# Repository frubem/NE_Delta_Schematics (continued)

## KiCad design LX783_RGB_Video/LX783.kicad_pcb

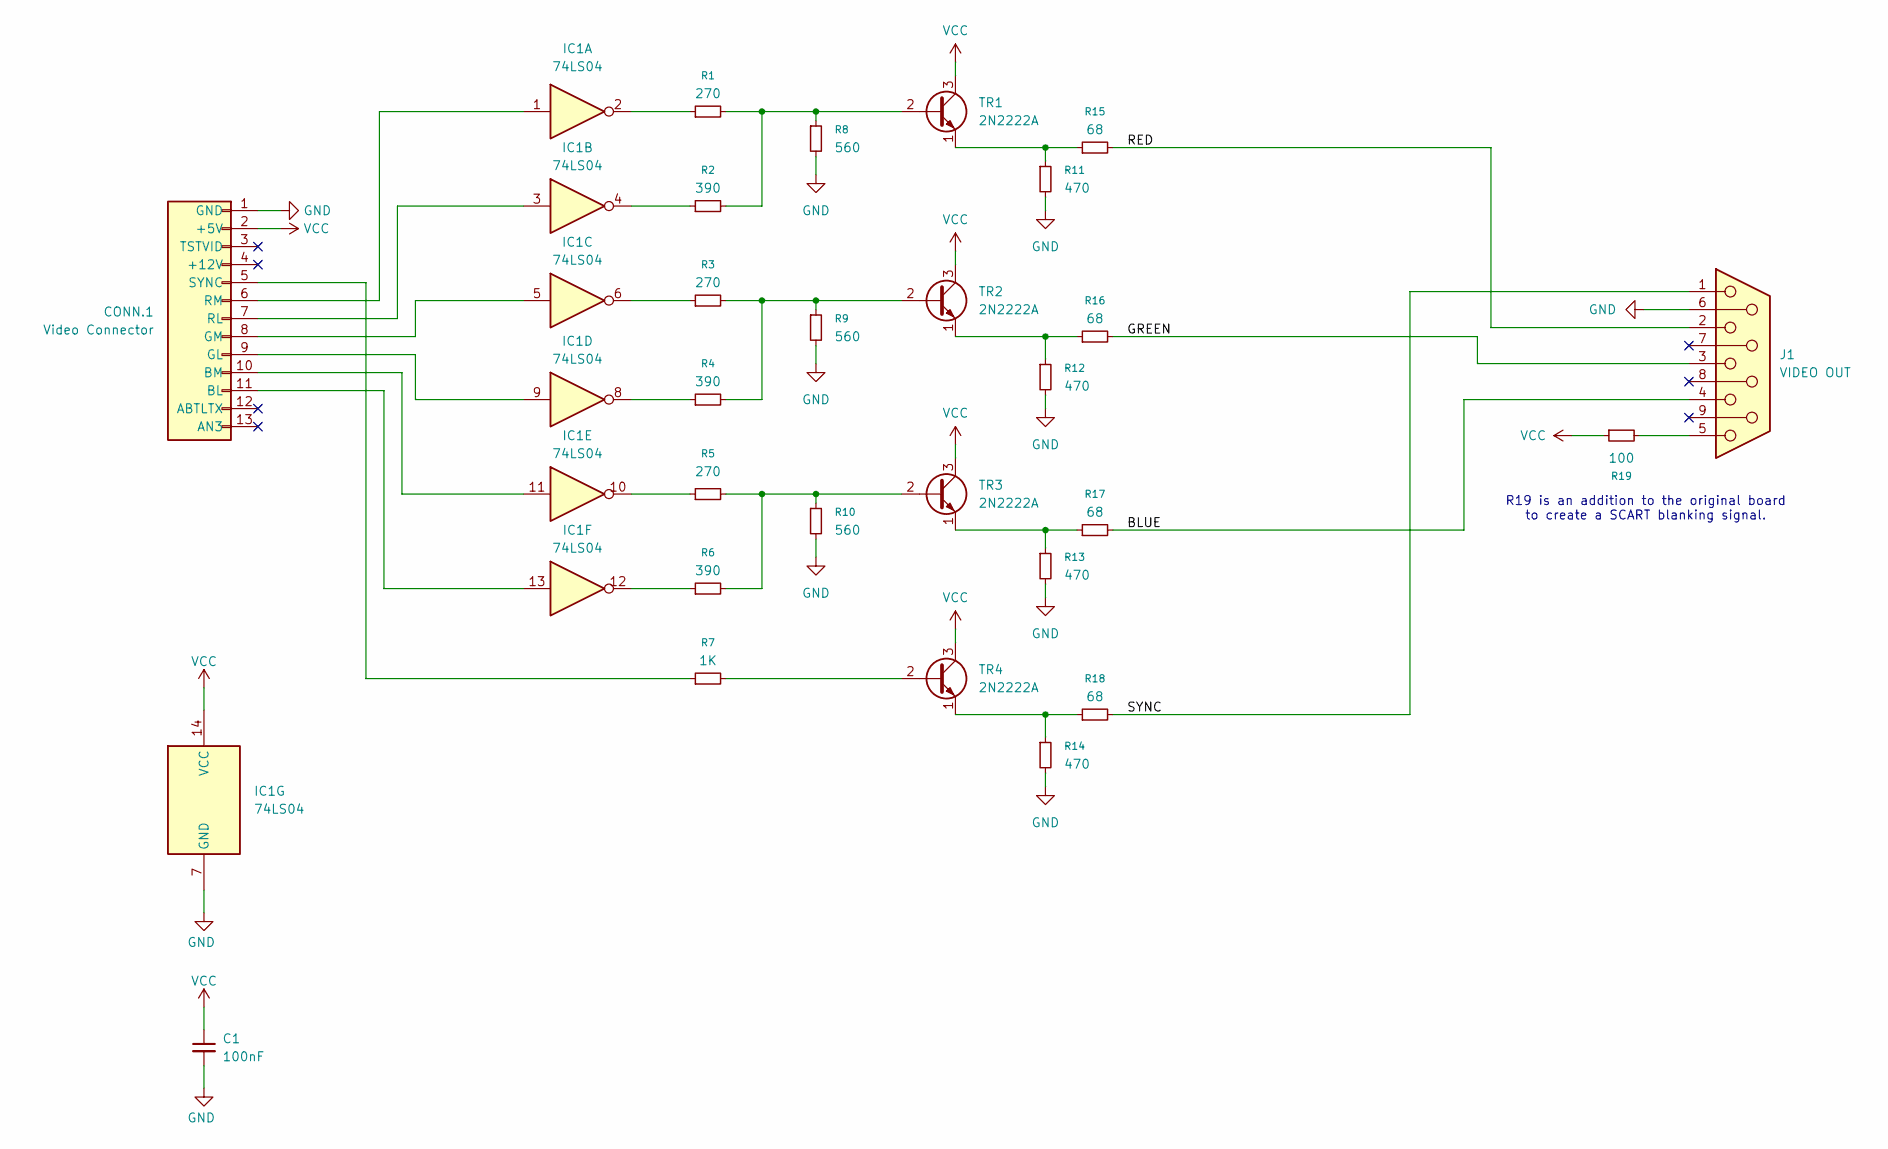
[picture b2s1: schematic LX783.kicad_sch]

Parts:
C1: 100nF; C_Disc_D6.0mm_W2.5mm_P5.00mm
CONN.1: Video Connector; PinHeader_1x13_P2.54mm_Horizontal
IC1: 74LS04; DIP-14_W7.62mm
J1: VIDEO OUT; DSUB-9_Socket_Horizontal
R1, R3, R5: 270; R_Axial_DIN0309_L9.0mm_D2.87mm_P12mm_Horizontal
R2, R4, R6: 390; R_Axial_DIN0309_L9.0mm_D2.87mm_P12mm_Horizontal
R7: 1K; R_Axial_DIN0309_L9.0mm_D2.87mm_P12mm_Horizontal
R8, R9, R10: 560; R_Axial_DIN0309_L9.0mm_D2.87mm_P12mm_Horizontal
R11, R12, R13, R14: 470; R_Axial_DIN0309_L9.0mm_D2.87mm_P12mm_Horizontal
R15, R16, R17, R18: 68; R_Axial_DIN0309_L9.0mm_D2.87mm_P12mm_Horizontal
R19: 100; R_Axial_DIN0309_L9.0mm_D2.87mm_P12mm_Horizontal
TR1, TR2, TR3, TR4: 2N2222A; TO-92_HandSolder

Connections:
/BLUE: J1.4, R17.2
/GREEN: J1.3, R16.2
/RED: J1.2, R15.2
/SYNC: J1.1, R18.2
GND: C1.2, CONN.1.1 (GND), IC1.7 (GND), J1.6, R8.2, R9.2, R10.2, R11.2, R12.2, R13.2, R14.2
unnamed: CONN.1.11 (BL), IC1.13
unnamed: CONN.1.10 (BM), IC1.11
unnamed: CONN.1.9 (GL), IC1.9
unnamed: CONN.1.8 (GM), IC1.5
unnamed: CONN.1.7 (RL), IC1.3
unnamed: CONN.1.6 (RM), IC1.1
unnamed: CONN.1.5 (SYNC), R7.1
unnamed: IC1.2, R1.1
unnamed: IC1.4, R2.1
unnamed: IC1.6, R3.1
unnamed: IC1.8, R4.1
unnamed: IC1.10, R5.1
unnamed: IC1.12, R6.1
unnamed: J1.5, R19.2
unnamed: R1.2, R2.2, R8.1, TR1.2 (B)
unnamed: R11.1, R15.1, TR1.1 (E)
unnamed: R3.2, R4.2, R9.1, TR2.2 (B)
unnamed: R12.1, R16.1, TR2.1 (E)
unnamed: R5.2, R6.2, R10.1, TR3.2 (B)
unnamed: R13.1, R17.1, TR3.1 (E)
unnamed: R7.2, TR4.2 (B)
unnamed: R14.1, R18.1, TR4.1 (E)
VCC: C1.1, CONN.1.2 (+5V), IC1.14 (VCC), R19.1, TR1.3 (C), TR2.3 (C), TR3.3 (C), TR4.3 (C)

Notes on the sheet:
R19 is an addition to the original board to create a SCART blanking signal.

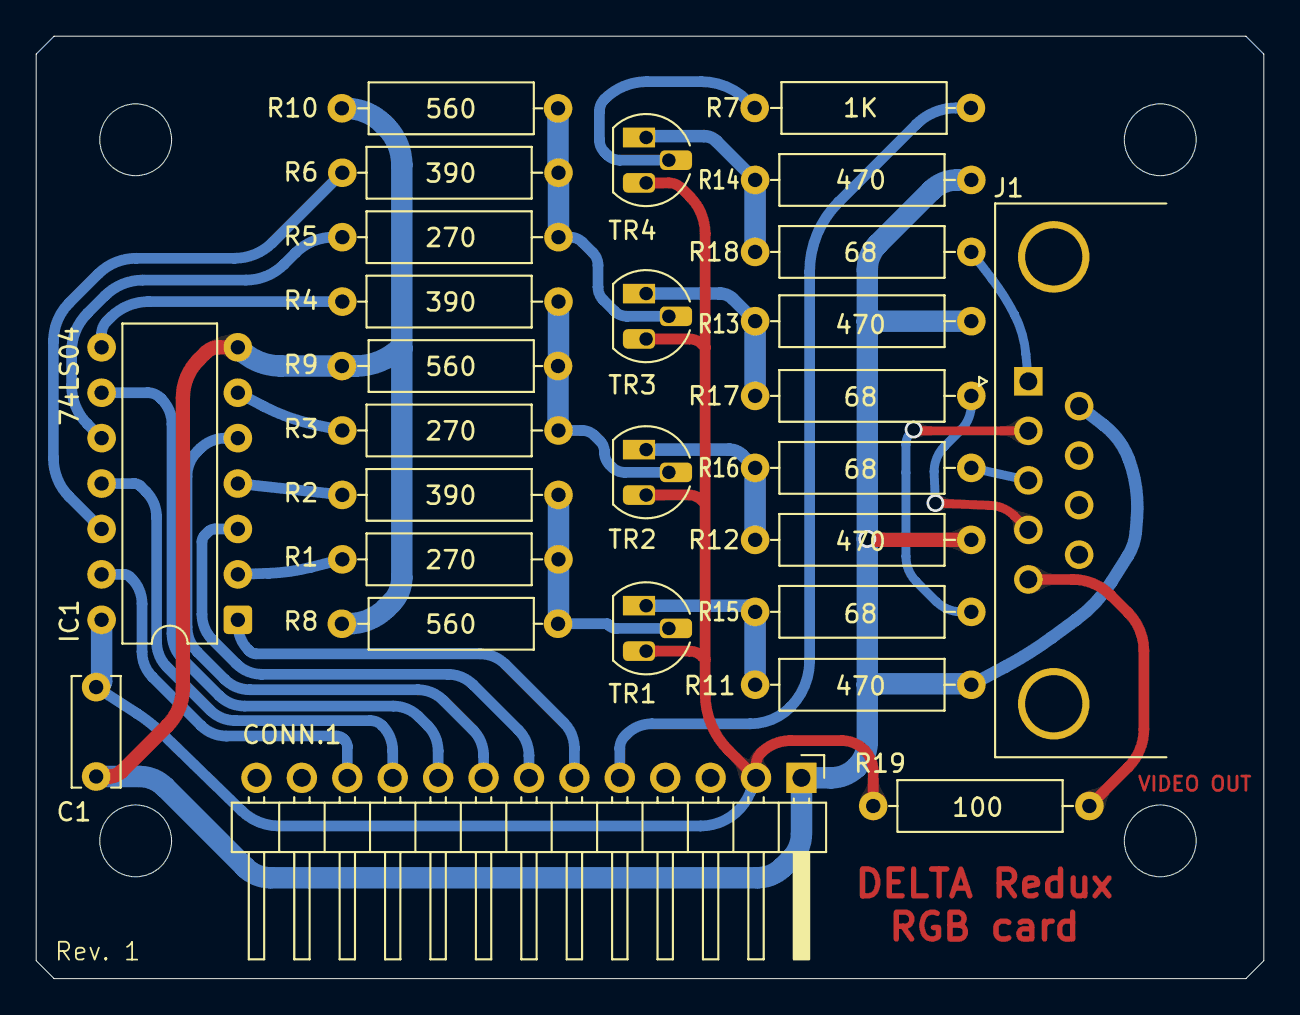
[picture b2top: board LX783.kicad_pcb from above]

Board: 2 copper layers, 68.7 x 52.7 mm, 27 parts (0 on the bottom side), 28 nets.

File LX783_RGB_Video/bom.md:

# LX783 RGB Video board - BOM

| Component              | Qty | Type / Value                                            | Notes                                                                |
| ---------------------- | --- | ------------------------------------------------------- | -------------------------------------------------------------------- |
| C1                     |  1  | 100nF/16V+ MLCC capacitor, 5mm pitch                    |                                                                      |
| CONN.1                 |  1  | pin header, 13P, 2.54mm pitch, right angle              |                                                                      |
| IC1                    |  1  | 74LS04 DIP-14                                           | Make sure to use an LS here, HCT works but colors will be off unless resistor values are adjusted |
| J1                     |  1  | DSUB-9 socket, horizontal                               |                                                                      |
| R1, R3, R5             |  3  | 270ohm resistor, 1/4W                                   |                                                                      |
| R2, R4, R5             |  3  | 390ohm resistor, 1/4W                                   |                                                                      |
| R7                     |  1  | 1Kohm resistor, 1/4W                                    |                                                                      |
| R8, R9, R10            |  3  | 560ohm resistor, 1/4W                                   |                                                                      |
| R11, R12, R13, R14     |  4  | 470ohm resistor, 1/4W                                   |                                                                      |
| R15, R16, R17, R18     |  4  | 68ohm resistor, 1/4W                                    |                                                                      |
| R19                    |  1  | 100ohm resistor, 1/4W                                   |                                                                      |
| TR1, TR2, TR3, TR4     |  4  | 2N2222A, TO-92                                          |                                                                      |

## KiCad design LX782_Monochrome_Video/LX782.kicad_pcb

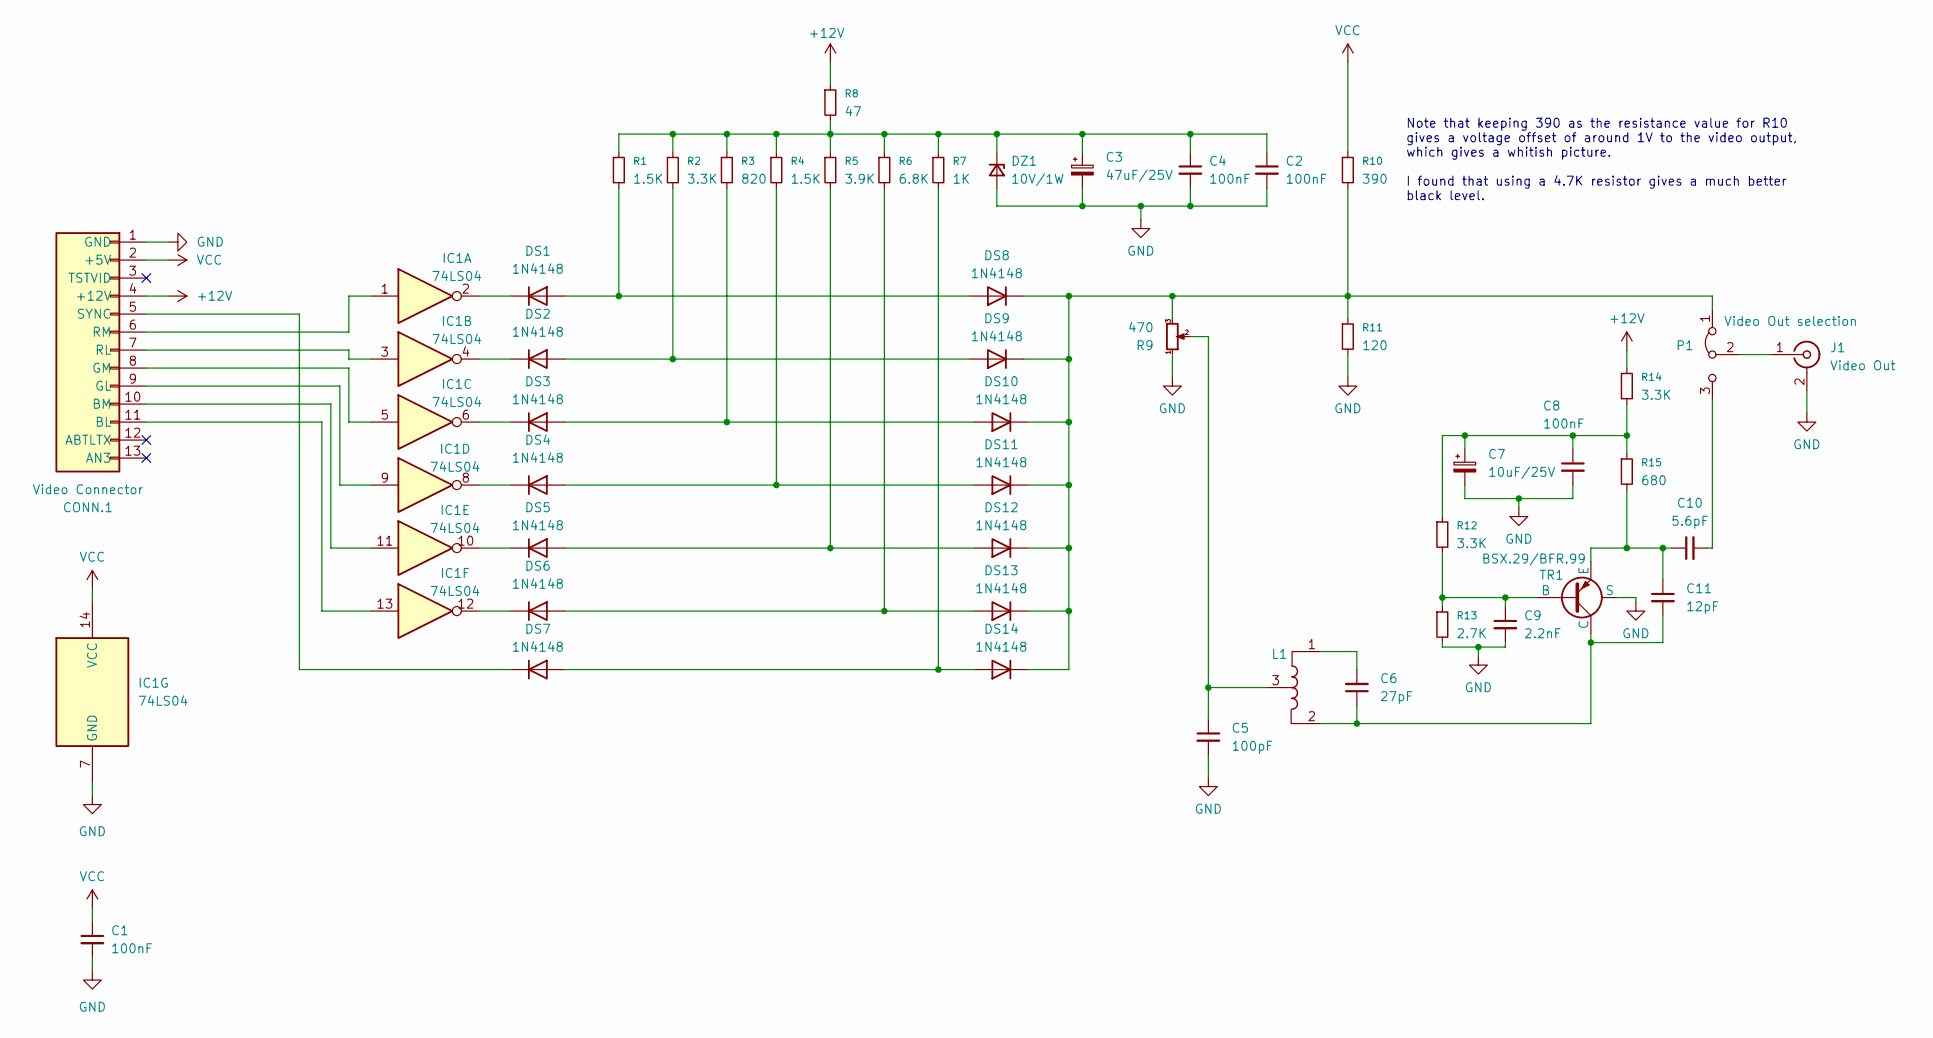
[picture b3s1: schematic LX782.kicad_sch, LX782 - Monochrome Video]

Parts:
C1, C2, C4, C8: 100nF; C_Disc_D6.0mm_W2.5mm_P5.00mm
C3: 47uF/25V; CP_Radial_D5.0mm_P2.50mm
C5: 100pF; C_Disc_D6.0mm_W2.5mm_P5.00mm
C6: 27pF; C_Disc_D6.0mm_W2.5mm_P5.00mm
C7: 10uF/25V; CP_Radial_D5.0mm_P2.50mm
C9: 2.2nF; C_Disc_D6.0mm_W2.5mm_P5.00mm
C10: 5.6pF; C_Disc_D6.0mm_W2.5mm_P5.00mm
C11: 12pF; C_Disc_D6.0mm_W2.5mm_P5.00mm
CONN.1: Video Connector; PinHeader_1x13_P2.54mm_Horizontal
DS1, DS2, DS3, DS4, DS5, DS6, DS7, DS8, DS9, DS10, DS11, DS12, DS13, DS14: 1N4148; D_DO-35_SOD27_P8mm_Horizontal
DZ1: 10V/1W; D_DO-35_SOD27_P8mm_Horizontal_BIGH
IC1: 74LS04; DIP-14_W7.62mm
J1: Video Out; Merlin_RCA
L1: Inductor_CenterTap; RF_Inductor
P1: Video Out selection; PinHeader_1x03_P2.54mm_Vertical
R1, R4: 1.5K; R_Axial_DIN0309_L9.0mm_D2.87mm_P10mm_Horizontal
R2, R12, R14: 3.3K; R_Axial_DIN0309_L9.0mm_D2.87mm_P10mm_Horizontal
R3: 820; R_Axial_DIN0309_L9.0mm_D2.87mm_P10mm_Horizontal
R5: 3.9K; R_Axial_DIN0309_L9.0mm_D2.87mm_P10mm_Horizontal
R6: 6.8K; R_Axial_DIN0309_L9.0mm_D2.87mm_P10mm_Horizontal
R7: 1K; R_Axial_DIN0309_L9.0mm_D2.87mm_P10mm_Horizontal
R8: 47; R_Axial_DIN0309_L9.0mm_D2.87mm_P10mm_Horizontal
R9: 470; Potentiometer_Bourns_3386P_Vertical
R10: 390; R_Axial_DIN0309_L9.0mm_D2.87mm_P10mm_Horizontal
R11: 120; R_Axial_DIN0309_L9.0mm_D2.87mm_P10mm_Horizontal
R13: 2.7K; R_Axial_DIN0309_L9.0mm_D2.87mm_P10mm_Horizontal
R15: 680; R_Axial_DIN0309_L9.0mm_D2.87mm_P10mm_Horizontal
TR1: BSX.29/BFR.99; TO72_BFR99

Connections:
+12V: CONN.1.4 (+12V), R8.1, R14.1
GND: C1.2, C2.2, C3.2, C4.2, C5.2, C7.2, C8.2, C9.2, CONN.1.1 (GND), DZ1.2 (A), IC1.7 (GND), J1.2 (Ext), R9.1, R11.2, R13.2, TR1.S
unnamed: C5.1, L1.3, R9.2
unnamed: C6.2, L1.1
unnamed: C7.1, C8.1, R12.1, R14.2, R15.1
unnamed: C9.1, R12.2, R13.1, TR1.B
unnamed: C10.1, C11.1, R15.2, TR1.E
unnamed: C6.1, C11.2, L1.2, TR1.C
unnamed: CONN.1.11 (BL), IC1.13
unnamed: CONN.1.10 (BM), IC1.11
unnamed: CONN.1.9 (GL), IC1.9
unnamed: CONN.1.8 (GM), IC1.5
unnamed: CONN.1.7 (RL), IC1.3
unnamed: CONN.1.6 (RM), IC1.1
unnamed: CONN.1.5 (SYNC), DS7.1 (K)
unnamed: DS1.2 (A), DS8.2 (A), R1.2
unnamed: DS1.1 (K), IC1.2
unnamed: DS2.2 (A), DS9.2 (A), R2.2
unnamed: DS2.1 (K), IC1.4
unnamed: DS3.1 (K), IC1.6
unnamed: DS4.1 (K), IC1.8
unnamed: DS5.1 (K), IC1.10
unnamed: DS6.1 (K), IC1.12
unnamed: DS3.2 (A), DS10.2 (A), R3.2
unnamed: DS8.1 (K), DS9.1 (K), DS10.1 (K), DS11.1 (K), DS12.1 (K), DS13.1 (K), DS14.1 (K), P1.1 (A), R9.3, R10.2, R11.1
unnamed: DS4.2 (A), DS11.2 (A), R4.2
unnamed: DS5.2 (A), DS12.2 (A), R5.2
unnamed: DS6.2 (A), DS13.2 (A), R6.2
unnamed: DS7.2 (A), DS14.2 (A), R7.2
unnamed: C2.1, C3.1, C4.1, DZ1.1 (K), R1.1, R2.1, R3.1, R4.1, R5.1, R6.1, R7.1, R8.2
unnamed: J1.1 (In), P1.2 (C)
unnamed: C10.2, P1.3 (B)
VCC: C1.1, CONN.1.2 (+5V), IC1.14 (VCC), R10.1

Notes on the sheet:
Note that keeping 390 as the resistance value for R10 gives a voltage offset of around 1V to the video output, which gives a whitish picture. I found that using a 4.7K resistor gives a much better black level.

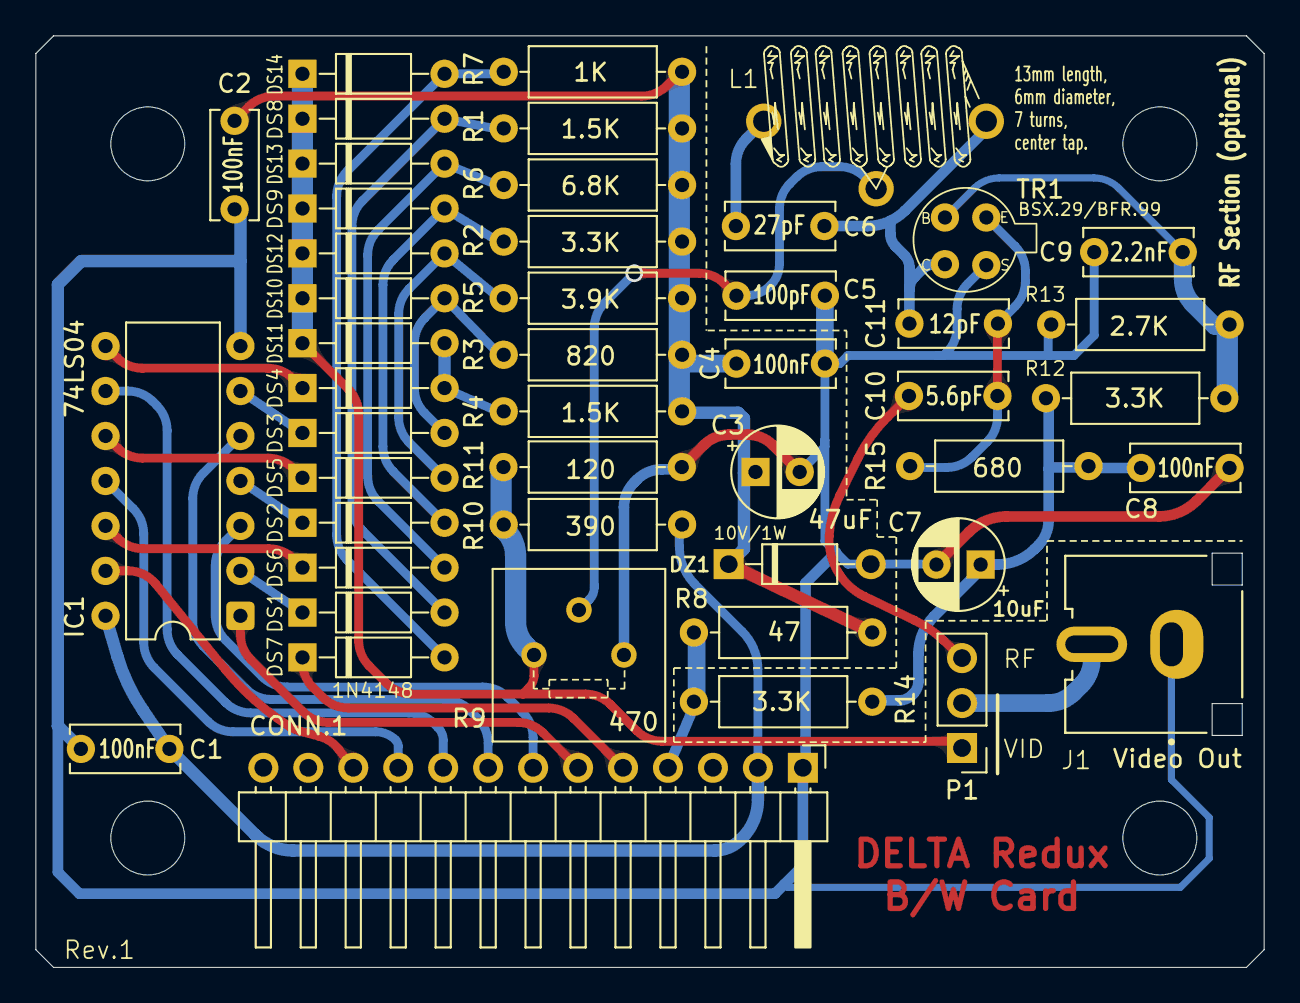
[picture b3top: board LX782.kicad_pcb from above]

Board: 2 copper layers, 69.4 x 52.6 mm, 47 parts (0 on the bottom side), 33 nets.

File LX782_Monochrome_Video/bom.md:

# LX782 TV/Composite Video board - BOM

| Component              | Qty | Type / Value                                            | Notes                                                                |
| ---------------------- | --- | ------------------------------------------------------- | -------------------------------------------------------------------- |
| C1, C2, C4             |  3  | 100nF/16V+ MLCC capacitor, 5mm pitch                    |                                                                      |
| C8		             |  1  | 100nF/25V+ MLCC capacitor, 5mm pitch                    | **RF section only.**                                                 |
| C3		             |  1  | 47uF/25V+ electrolytic capacitor, 2.5mm pitch           |                                                                      |
| C5		             |  1  | 100pF/25V+ MLCC capacitor, 5mm pitch                    | **RF section only.**                                                 |
| C6		             |  1  | 27pF/25V+ MLCC capacitor, 5mm pitch                     | **RF section only.**                                                 |
| C7		             |  1  | 10uF/25V+ electrolytic capacitor, 2.5mm pitch           | **RF section only.**                                                 |
| C9		             |  1  | 2.2nF/25V+ MLCC capacitor, 5mm pitch                    | **RF section only.**                                                 |
| C10		             |  1  | 5.6pF/25V+ MLCC capacitor, 5mm pitch                    | **RF section only.**                                                 |
| C11		             |  1  | 12pF/25V+ MLCC capacitor, 5mm pitch                     | **RF section only.**                                                 |
| CONN.1                 |  1  | pin header, 13P, 2.54mm pitch, right angle              |                                                                      |
| IC1                    |  1  | 74LS04 DIP-14                                           | 'HCT can be used                                                     |
| DS1 - DS14             |  14 | 1N4148                                                  |                                                                      |
| DZ1                    |  1  | 10V/1W zener diode, DO-35                               | 1N4740A is fine for this                                             |
| J1                     |  1  | RCA connector, yellow, merlin style                     | You can find these on [AliExpress](https://aliexpress.com/item/1005006135848173.html) or RCJ-042 on Mouser |
| L1                     |  1  | Handwound inductor                                      | **RF section only.**  Use 0.5mm copper wire, wind 7 spires on a 6mm diameter cilinder, pull the wire to make the inductor 13mm long. Make a center tap at 3.5 windings |
| P1                     |  1  | Video output selection. 3P, 2.54mm header               | If RF section is omitted, solder pin 1 and 2 together.               |
| R1                     |  1  | 1.5Kohm resistor, 1/4W                                  |                                                                      |
| R2                     |  1  | 3.3Kohm resistor, 1/4W                                  |                                                                      |
| R3                     |  1  | 820ohm resistor, 1/4W                                   |                                                                      |
| R4                     |  1  | 820ohm resistor, 1/4W                                   |                                                                      |
| R5                     |  1  | 3.9Kohm resistor, 1/4W                                  |                                                                      |
| R6                     |  1  | 6.8Kohm resistor, 1/4W                                  |                                                                      |
| R7                     |  1  | 1Kohm resistor, 1/4W                                    |                                                                      |
| R8                     |  1  | 47ohm resistor, 1/4W                                    |                                                                      |
| R9                     |  1  | 470ohm resistor, Bourns 3386 potentiometer              | If RF section is omitted, wire a 470ohm resistor across the two bottom pins. |
| R10                    |  1  | 390ohm resistor, 1/4W                                   | Original BOM calls for 390ohm, which generates too hot of a signal. It may be a typo and be originally 3.9K. It is advised to replace it with a 4.7Kohm                                                                     |
| R11                    |  1  | 120ohm resistor, 1/4W                                   |                                                                      |
| R12, R14               |  2  | 3.3Kohm resistor, 1/4W                                  | **RF section only.**                                                 |
| R13                    |  1  | 2.7Kohm resistor, 1/4W                                  | **RF section only.**                                                 |
| R15                    |  1  | 680ohm resistor, 1/4W                                   | **RF section only.**                                                 |
| TR1				     |  1  | BSX.29/BFR.99 TO-72                                     | **RF section only.**                                                                     |

The RF section builds a VHF modulator. Unless you want to connect it to a TV via the antenna port, it is useless to build.

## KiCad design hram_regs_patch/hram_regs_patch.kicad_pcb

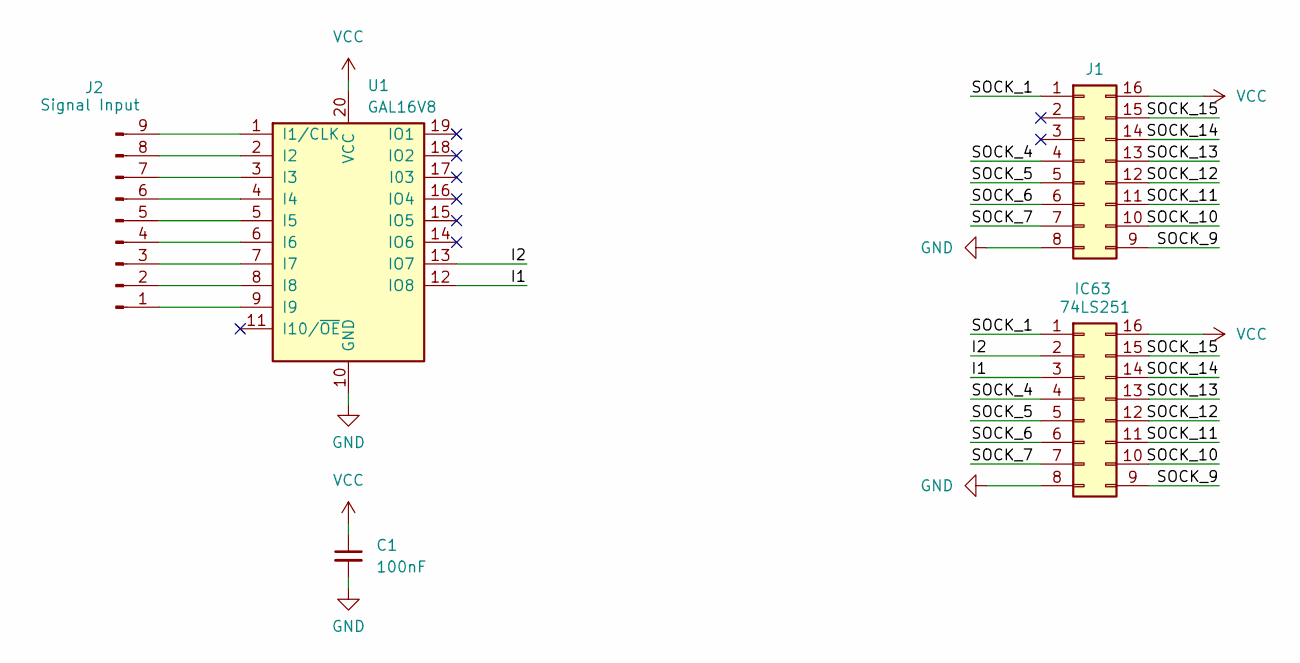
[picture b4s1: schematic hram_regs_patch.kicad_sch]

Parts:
C1: 100nF; C_Disc_D4.3mm_W1.9mm_P5.00mm
IC63: 74LS251; DIP-16_W7.62mm
J1: reversed_DIP-16_W7.62mm
J2: Signal Input; PinHeader_1x09_P2.54mm_Horizontal
U1: GAL16V8; DIP-20_W7.62mm

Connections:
/I1: IC63.3, U1.12 (IO8)
/I2: IC63.2, U1.13 (IO7)
/SOCK_1: IC63.1, J1.1
/SOCK_4: IC63.4, J1.4
/SOCK_5: IC63.5, J1.5
/SOCK_6: IC63.6, J1.6
/SOCK_7: IC63.7, J1.7
/SOCK_9: IC63.9, J1.9
/SOCK_10: IC63.10, J1.10
/SOCK_11: IC63.11, J1.11
/SOCK_12: IC63.12, J1.12
/SOCK_13: IC63.13, J1.13
/SOCK_14: IC63.14, J1.14
/SOCK_15: IC63.15, J1.15
GND: C1.2, IC63.8, J1.8, U1.10 (GND)
unnamed: J2.1, U1.9 (I9)
unnamed: J2.2, U1.8 (I8)
unnamed: J2.3, U1.7 (I7)
unnamed: J2.4, U1.6 (I6)
unnamed: J2.5, U1.5 (I5)
unnamed: J2.6, U1.4 (I4)
unnamed: J2.7, U1.3 (I3)
unnamed: J2.8, U1.2 (I2)
unnamed: J2.9, U1.1 (I1/CLK)
VCC: C1.1, IC63.16, J1.16, U1.20 (VCC)

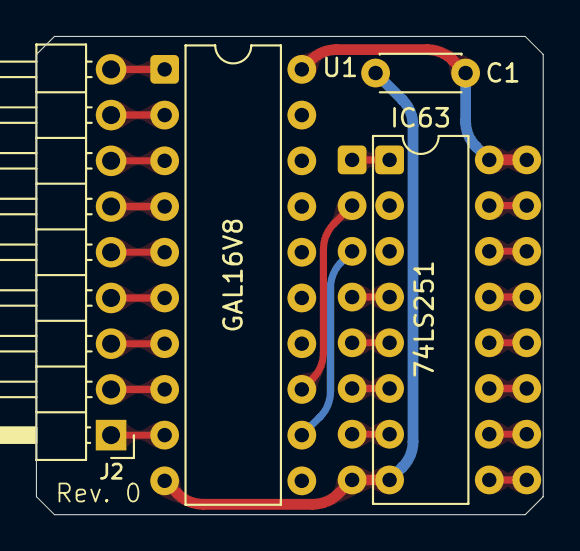
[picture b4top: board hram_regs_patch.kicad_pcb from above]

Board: 2 copper layers, 28.2 x 26.6 mm, 5 parts (0 on the bottom side), 25 nets.
